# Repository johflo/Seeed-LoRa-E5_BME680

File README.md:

Seeed Wio E5 LoraWan BME680 node without seperate MCU.
Data from the BM680 is sent through the Helium LoraWan network to Cayenne to visualize the measured data

PCB designed with KiCad, assembled by seeedstudio (https://github.com/Seeed-Studio)

Next steps todo:
- testing low power consumption (low current measurement equipment needed like https://github.com/nfhw/tinycurrent)
- rework pcb to shrink it
- connection to Datacake instead of directly to Helium

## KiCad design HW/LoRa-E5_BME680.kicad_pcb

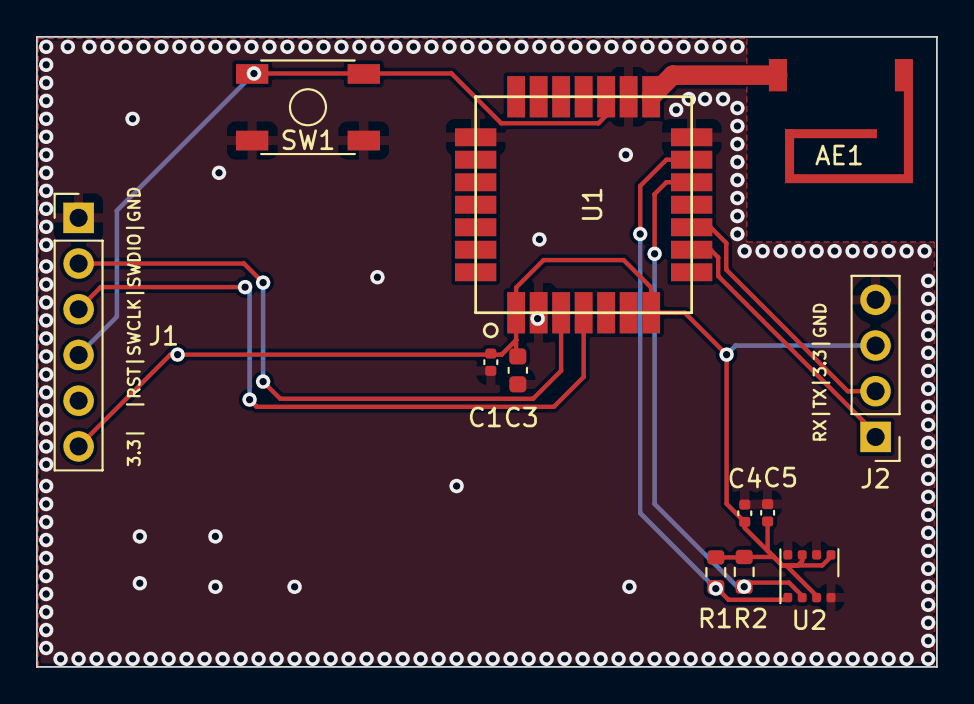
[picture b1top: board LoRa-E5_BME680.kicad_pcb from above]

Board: 2 copper layers, 50.0 x 35.0 mm, 13 parts (1 on the bottom side), 10 nets.

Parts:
AE1: Antenna; Johanson 0868AT43A0020
BT1: Battery_Cell; BatteryHolder_Keystone_3008_1x2450
C1, C4, C5: 100nF; C_0402_1005Metric
C3: 4.7µF; C_0603_1608Metric
J1: Conn_01x06; PinHeader_1x06_P2.54mm_Vertical
J2: Conn_01x04; PinHeader_1x04_P2.54mm_Vertical
R1, R2: 4k7; R_0603_1608Metric
SW1: RST; Alps 5.2x5.2
U1: LoRa-E5
U2: BME680; Bosch_LGA-8_3x3mm_P0.8mm_ClockwisePinNumbering

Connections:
+3V3: BT1.1 (+), C1.1, C3.1, C4.2, C5.2, J1.6, J2.3, R1.2, R2.2, U1.1 (VCC), U1.7 (PB4), U2.2 (CSB), U2.6 (VDDIO), U2.8 (VDD)
Antenna: AE1.1 (A), U1.15 (RFIO)
GND: BT1.2 (-), C1.2, C3.2, C4.1, C5.1, J1.1, J2.4, SW1.2, U1.2 (GND), U1.14 (GND), U1.16 (GND), U1.22 (GND), U2.1 (GND), U2.5 (SDO), U2.7 (GND)
PA13/SWDIO: J1.2, U1.3 (PA13)
PA14/SWCLK: J1.3, U1.4 (PA14)
PB6/TX: J2.2, U1.10 (PB6)
PB7/RX: J2.1, U1.9 (PB7)
PC0/SCL: R1.1, U1.13 (PC0), U2.4 (SCK)
PC1/SDA: R2.1, U1.12 (PC1), U2.3 (SDI)
RST: J1.4, SW1.1, U1.17 (RST)

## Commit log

2023-09-19 First release
2023-09-20 Upload HW files
2023-09-21 Set LoRaWAN region to Europe
